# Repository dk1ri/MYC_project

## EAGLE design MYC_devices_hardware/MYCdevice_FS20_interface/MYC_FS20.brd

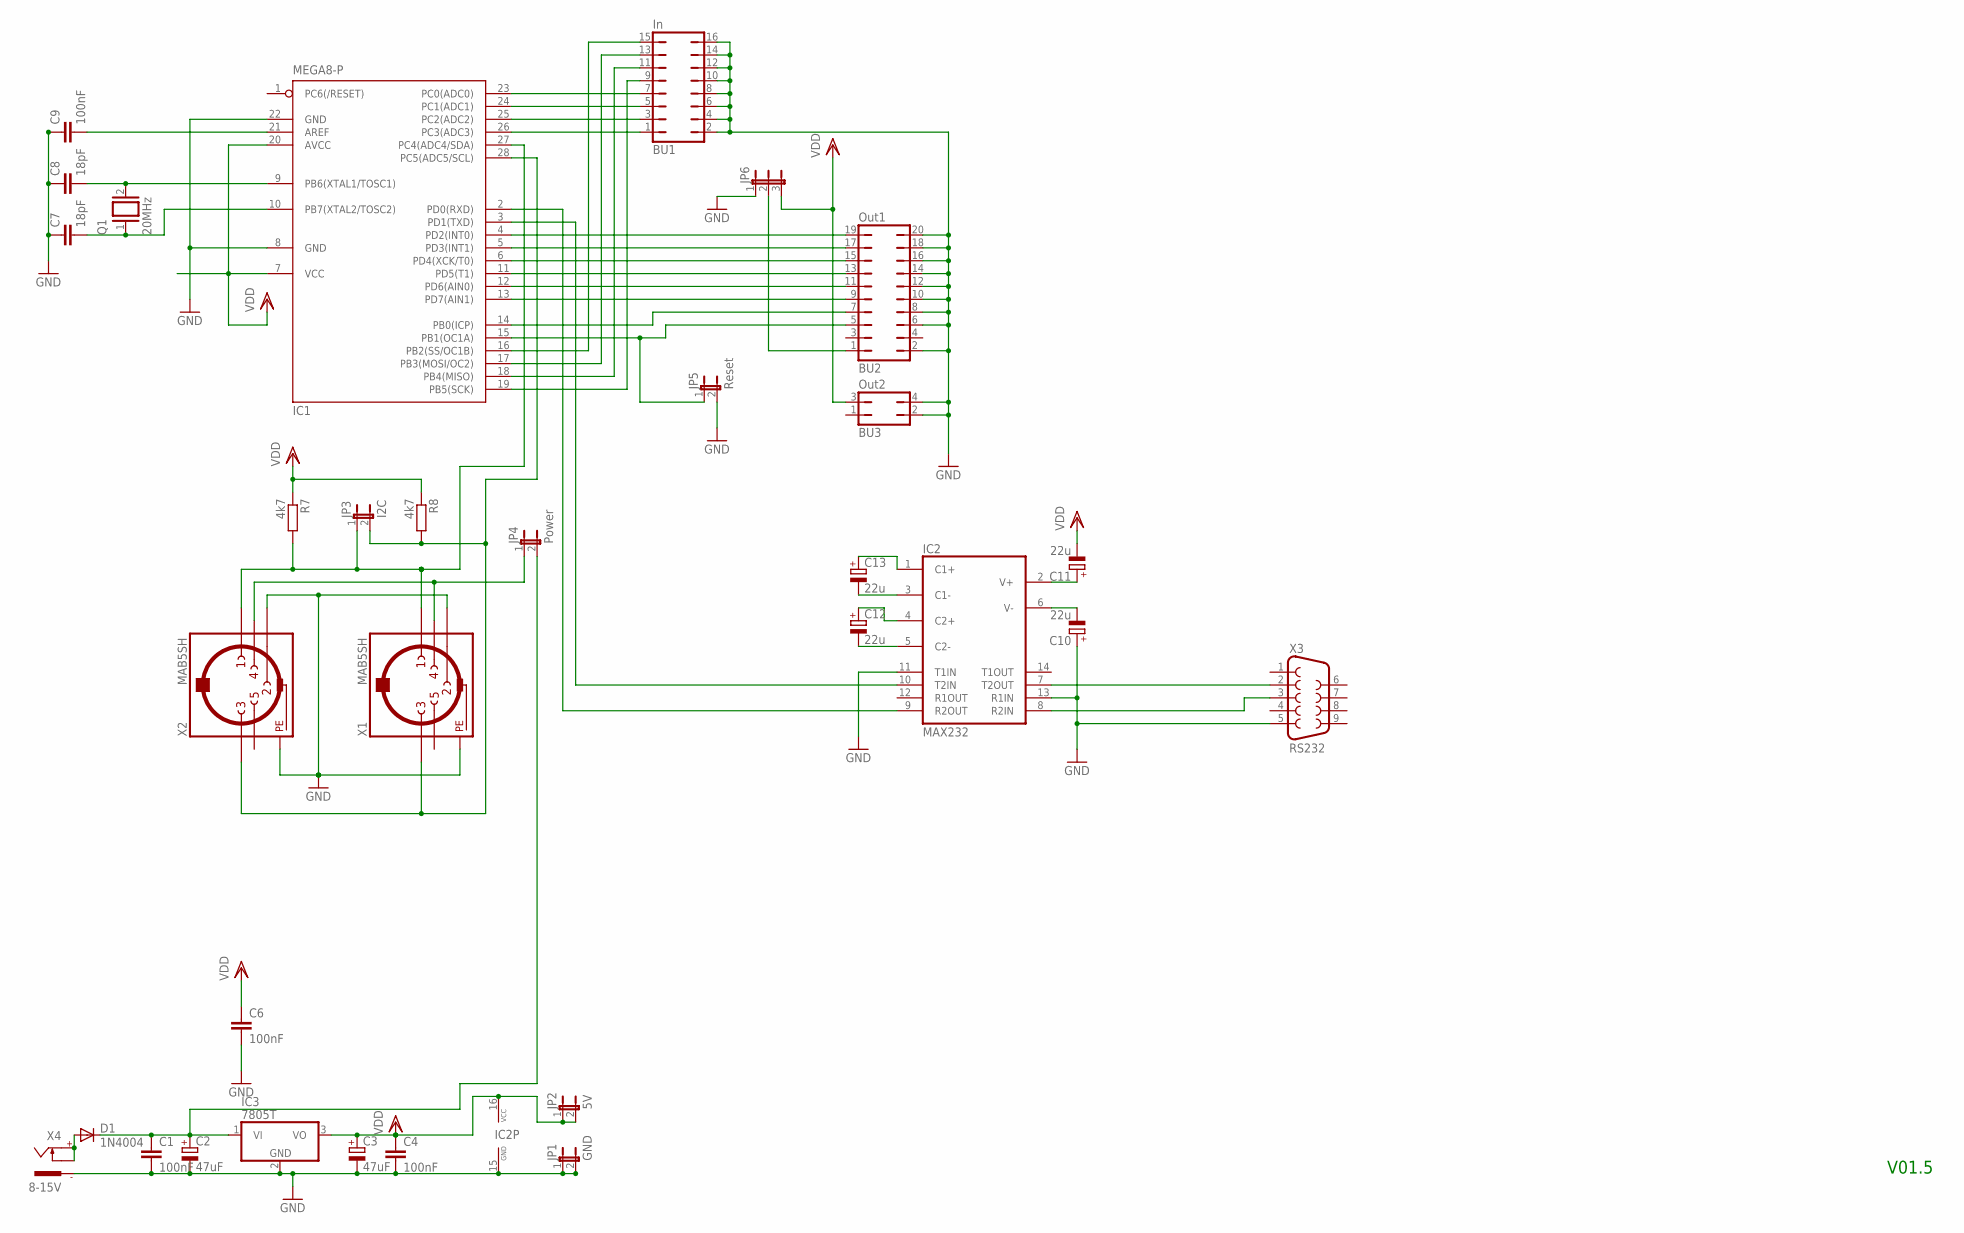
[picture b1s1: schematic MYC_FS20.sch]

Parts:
BU1: In; JP8Q
BU2: Out1; JP10Q
BU3: Out2; JP2Q
C1, C4, C6, C9: 100nF; C050-025X075
C2, C3: 47uF; TT5D10
C7, C8: 18pF; C050-025X075
C10, C11, C12, C13: 22u; TT5D7
D1: 1N4004; DO41-10
IC1: MEGA8-P; DIL28-3
IC2: MAX232; DIL16
IC3: 7805T; TO220H
JP1: GND; JP1
JP2: 5V; JP1
JP3: I2C; JP1
JP4: Power; JP1
JP5: Reset; JP1
JP6: JP2E; JP2
Q1: 20MHz; QS
R7, R8: 4k7; 0207/5V
X1, X2: MAB5SH
X3: RS232; F09H
X4: 8-15V; 737992-5

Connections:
C13: C13.+, IC2.1 (C1+)
GND: BU1.2, BU1.4, BU1.6, BU1.8, BU1.10, BU1.12, BU1.14, BU1.16, BU2.2, BU2.6, BU2.8, BU2.10, BU2.12, BU2.14, BU2.16, BU2.18, BU2.20, BU3.2, BU3.4, C1.2, C2.-, C3.-, C4.2, C6.2, C7.1, C8.1, C9.1, C10.+, IC1.8 (GND), IC1.22 (GND), IC2.11 (T1IN), IC2.13 (R1IN), IC2.15 (GND), IC3.2 (GND), JP1.1, JP1.2, JP5.2, JP6.1, X1.2, X1.PE, X1.PE@ (PE), X2.2, X2.PE, X2.PE@ (PE), X3.5, X4.-1
unnamed: JP4.1, X1.4, X2.4
unnamed: IC1.2 (PD0(RXD)), IC2.9 (R2OUT)
unnamed: C12.-, IC2.5 (C2-)
unnamed: BU2.11, IC1.12 (PD6(AIN0))
unnamed: IC1.27 (PC4(ADC4/SDA)), JP3.1, R7.2, X1.1, X2.1
unnamed: BU1.1, IC1.26 (PC3(ADC3))
unnamed: D1.A, X4.+, X4.K
unnamed: BU2.7, IC1.14 (PB0(ICP))
unnamed: BU2.1, JP6.2
unnamed: IC2.8 (R2IN), X3.3
unnamed: IC1.3 (PD1(TXD)), IC2.10 (T2IN)
unnamed: C12.+, IC2.4 (C2+)
unnamed: C13.-, IC2.3 (C1-)
unnamed: BU1.3, IC1.25 (PC2(ADC2))
unnamed: C11.+, IC2.2 (V+)
unnamed: C10.-, IC2.6 (V-)
unnamed: BU2.5, IC1.15 (PB1(OC1A)), JP5.1
unnamed: C8.2, IC1.9 (PB6(XTAL1/TOSC1)), Q1.2
unnamed: BU1.5, IC1.24 (PC1(ADC1))
unnamed: BU2.9, IC1.13 (PD7(AIN1))
unnamed: IC1.28 (PC5(ADC5/SCL)), JP3.2, R8.2, X1.3, X2.3
unnamed: BU1.7, IC1.23 (PC0(ADC0))
unnamed: BU2.13, IC1.11 (PD5(T1))
unnamed: BU2.15, IC1.6 (PD4(XCK/T0))
unnamed: IC2.7 (T2OUT), X3.2
unnamed: BU2.17, IC1.5 (PD3(INT1))
unnamed: BU2.19, IC1.4 (PD2(INT0))
unnamed: BU1.15, IC1.16 (PB2(SS/OC1B))
unnamed: C1.1, C2.+, D1.C, IC3.1 (VI), JP4.2
unnamed: BU1.13, IC1.17 (PB3(MOSI/OC2))
unnamed: C9.2, IC1.21 (AREF)
unnamed: BU1.11, IC1.18 (PB4(MISO))
unnamed: C7.2, IC1.10 (PB7(XTAL2/TOSC2)), Q1.1
unnamed: BU1.9, IC1.19 (PB5(SCK))
VDD: BU3.3, C3.+, C4.1, C6.1, C11.-, IC1.7 (VCC), IC1.20 (AVCC), IC2.16 (VCC), IC3.3 (VO), JP2.1, JP2.2, JP6.3, R7.1, R8.1

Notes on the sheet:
V01.5

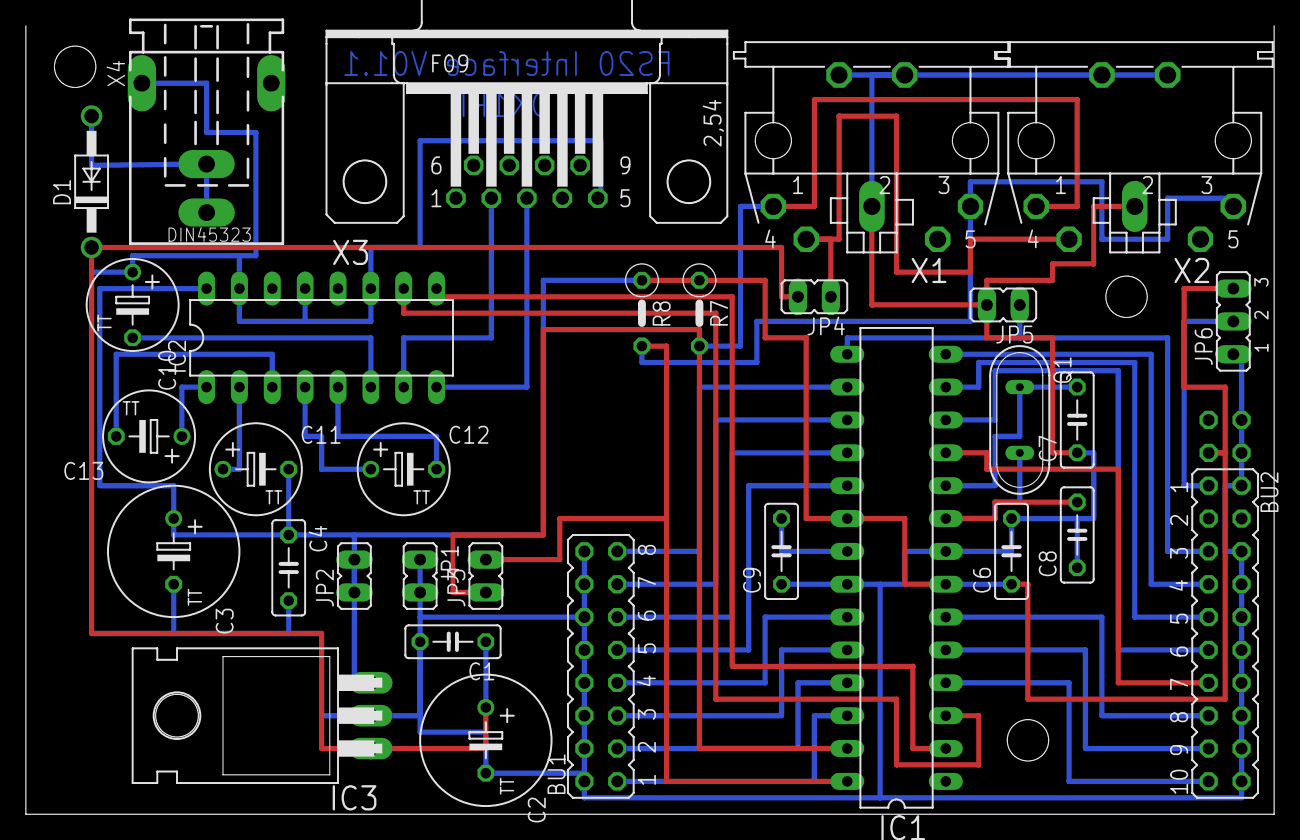
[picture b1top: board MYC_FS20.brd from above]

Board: 2 copper layers, 96.5 x 60.9 mm, 32 parts (1 on the bottom side), 37 nets.

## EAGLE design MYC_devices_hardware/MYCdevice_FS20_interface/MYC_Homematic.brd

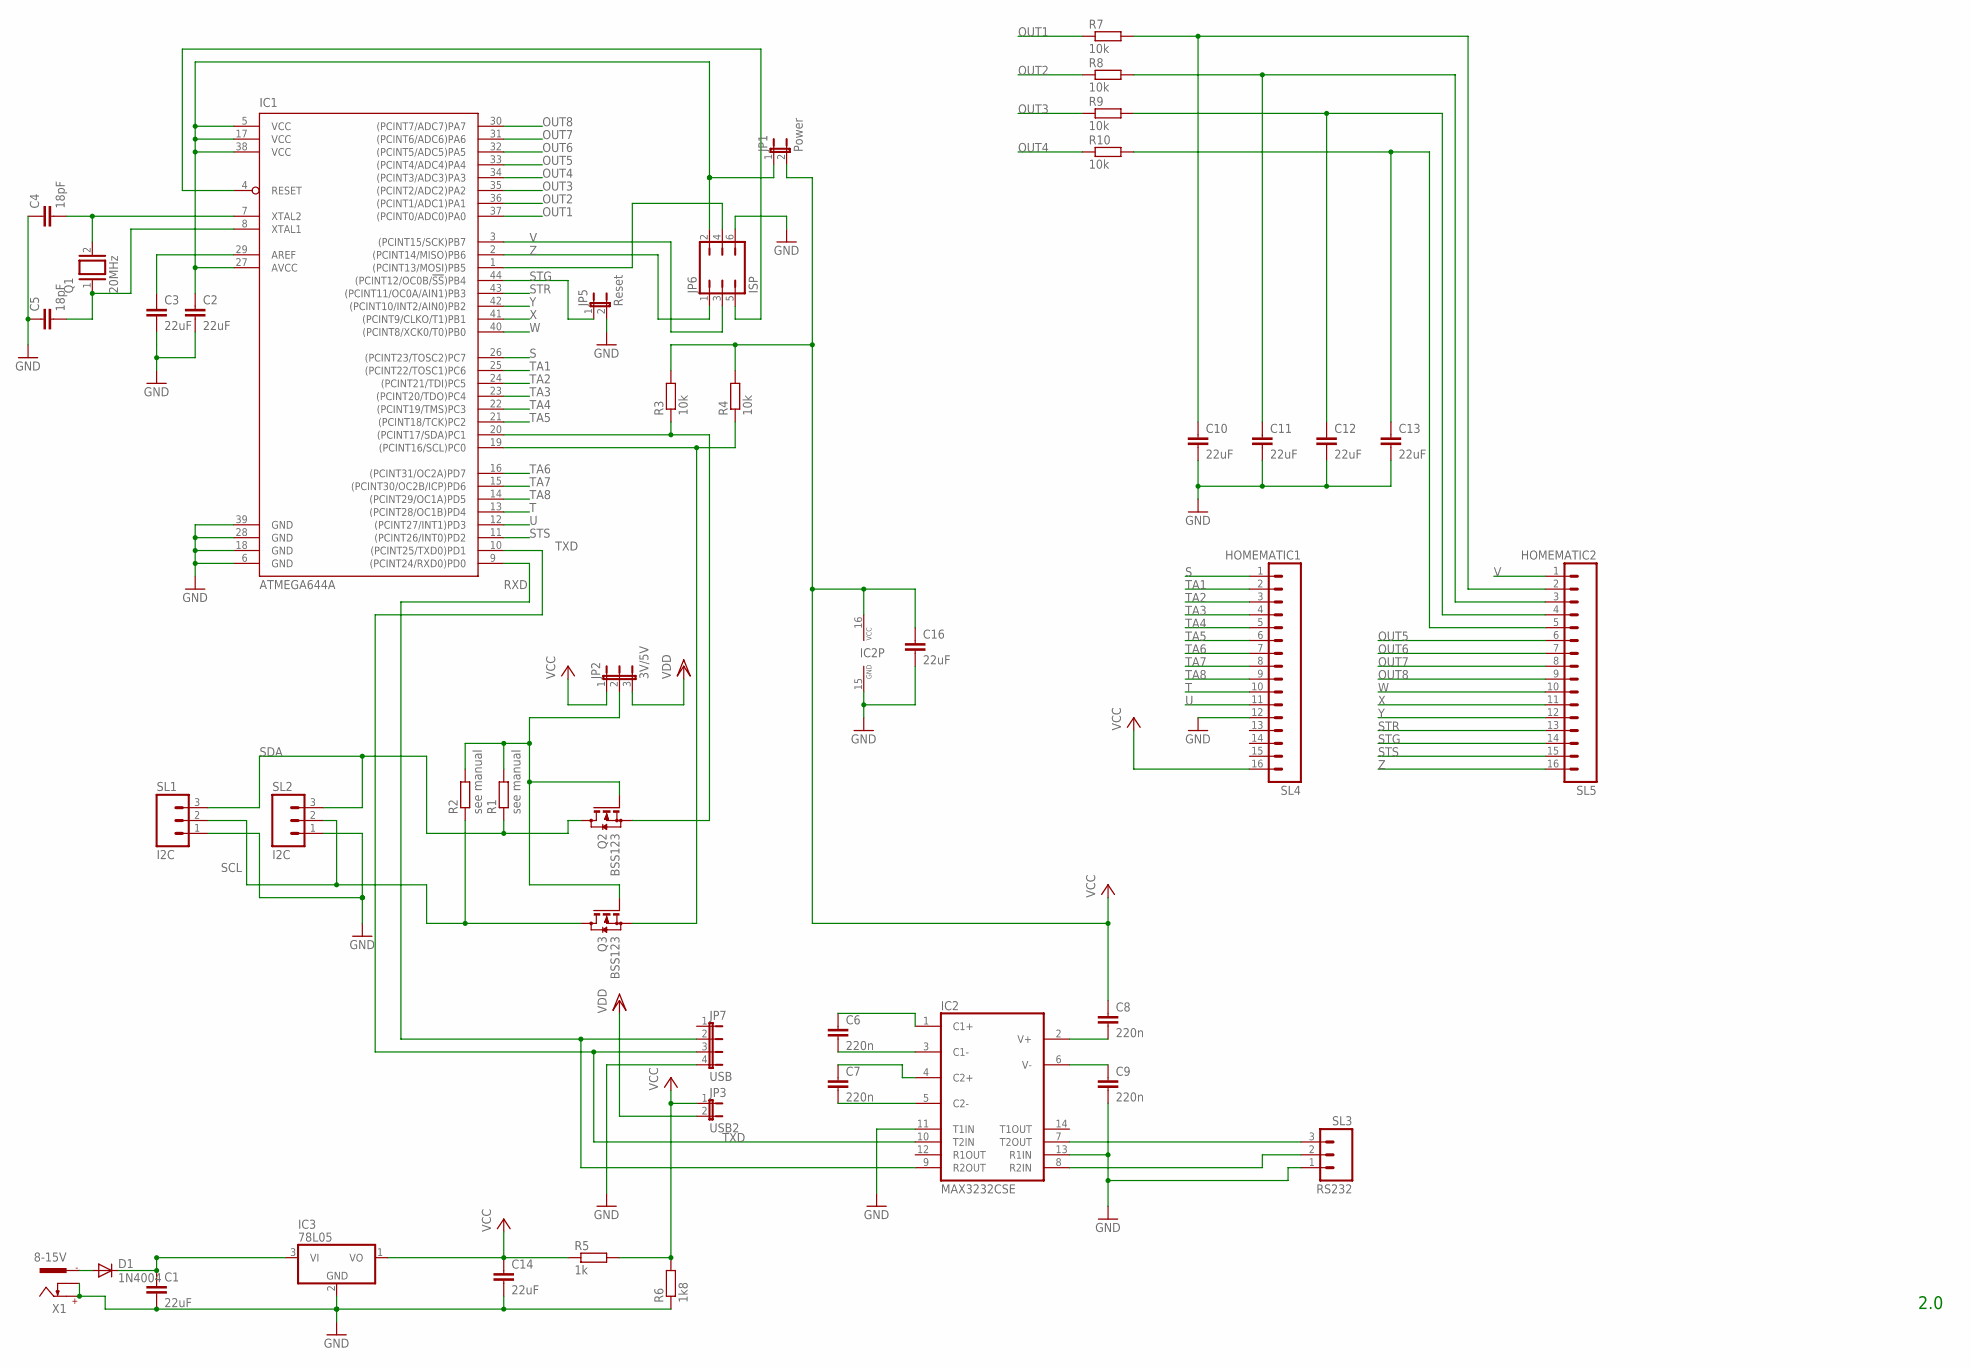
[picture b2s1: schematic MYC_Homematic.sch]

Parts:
C1, C2, C3, C10, C11, C12, C13, C14, C16: 22uF; C1206
C4, C5: 18pF; C025-030X050
C6, C7, C8, C9: 220n; C1206
D1: 1N4004; DO41-10
IC1: ATMEGA644A; TQFP44
IC2: MAX3232CSE; SO16
IC3: 78L05; TO92
JP1: Power; JP1
JP2: 3V/5V; JP2
JP3: USB2; JP1
JP5: Reset; JP1
JP6: ISP; JP3Q
JP7: USB; JP4
Q1: 20MHz; QS
Q2, Q3: BSS123; SOT23
R1, R2: see manual; R1206
R3, R4, R7, R8, R9, R10: 10k; R1206
R5: 1k; R1206
R6: 1k8; R1206
SL1, SL2: I2C; 03P
SL3: RS232; 03P
SL4: HOMEMATIC1; 16P
SL5: HOMEMATIC2; 16P
X1: 8-15V; 737992-5

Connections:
C13: C6.1, IC2.1 (C1+)
GND: C1.2, C2.2, C3.2, C4.1, C5.1, C9.2, C10.2, C11.2, C12.2, C13.2, C14.2, C16.2, IC1.6 (GND), IC1.18 (GND), IC1.28 (GND), IC1.39 (GND), IC2.11 (T1IN), IC2.13 (R1IN), IC2.15 (GND), IC3.2 (GND), JP5.2, JP6.6, JP7.4, R6.1, SL1.1, SL2.1, SL3.1, SL4.12, X1.+, X1.K
unnamed: C1.1, D1.C, IC3.3 (VI)
unnamed: C7.2, IC2.5 (C2-)
unnamed: JP2.2, Q2.1 (G), Q3.1 (G), R1.2, R2.2
unnamed: IC1.19 ((PCINT16/SCL)PC0), Q3.2 (S), R4.1
unnamed: C3.1, IC1.29 (AREF)
unnamed: C2.1, IC1.5 (VCC), IC1.17 (VCC), IC1.27 (AVCC), IC1.38 (VCC), JP1.1, JP6.2
unnamed: IC1.20 ((PCINT17/SDA)PC1), Q2.2 (S), R3.1
unnamed: D1.A, X1.-1
unnamed: IC2.8 (R2IN), SL3.2
unnamed: IC1.1 ((PCINT13/MOSI)PB5), JP6.4
unnamed: C7.1, IC2.4 (C2+)
unnamed: C6.2, IC2.3 (C1-)
unnamed: C10.1, R7.2, SL5.2
unnamed: C8.2, IC2.2 (V+)
unnamed: C9.1, IC2.6 (V-)
unnamed: C4.2, IC1.7 (XTAL2), Q1.2
unnamed: C11.1, R8.2, SL5.3
unnamed: C12.1, R9.2, SL5.4
unnamed: C13.1, R10.2, SL5.5
unnamed: IC1.4 (RESET), JP6.5
unnamed: IC2.7 (T2OUT), SL3.3
unnamed: C5.2, IC1.8 (XTAL1), Q1.1
OUT1: IC1.37 ((PCINT0/ADC0)PA0), R7.1
OUT2: IC1.36 ((PCINT1/ADC1)PA1), R8.1
OUT3: IC1.35 ((PCINT2/ADC2)PA2), R9.1
OUT4: IC1.34 ((PCINT3/ADC3)PA3), R10.1
OUT5: IC1.33 ((PCINT4/ADC4)PA4), SL5.6
OUT6: IC1.32 ((PCINT5/ADC5)PA5), SL5.7
OUT7: IC1.31 ((PCINT6/ADC6)PA6), SL5.8
OUT8: IC1.30 ((PCINT7/ADC7)PA7), SL5.9
RXD: IC1.9 ((PCINT24/RXD0)PD0), IC2.9 (R2OUT), JP7.2
S: IC1.26 ((PCINT23/TOSC2)PC7), SL4.1
SCL: Q3.3 (D), R2.1, SL1.2, SL2.2
SDA: Q2.3 (D), R1.1, SL1.3, SL2.3
STG: IC1.44 ((PCINT12/OC0B/!SS!)PB4), JP5.1, SL5.14
STR: IC1.43 ((PCINT11/OC0A/AIN1)PB3), SL5.13
STS: IC1.11 ((PCINT26/INT0)PD2), SL5.15
T: IC1.13 ((PCINT28/OC1B)PD4), SL4.10
TA1: IC1.25 ((PCINT22/TOSC1)PC6), SL4.2
TA2: IC1.24 ((PCINT21/TDI)PC5), SL4.3
TA3: IC1.23 ((PCINT20/TDO)PC4), SL4.4
TA4: IC1.22 ((PCINT19/TMS)PC3), SL4.5
TA5: IC1.21 ((PCINT18/TCK)PC2), SL4.6
TA6: IC1.16 ((PCINT31/OC2A)PD7), SL4.7
TA7: IC1.15 ((PCINT30/OC2B/ICP)PD6), SL4.8
TA8: IC1.14 ((PCINT29/OC1A)PD5), SL4.9
TXD: IC1.10 ((PCINT25/TXD0)PD1), IC2.10 (T2IN), JP7.3
U: IC1.12 ((PCINT27/INT1)PD3), SL4.11
V: IC1.3 ((PCINT15/SCK)PB7), JP6.3, SL5.1
VCC: C8.1, C14.1, C16.1, IC2.16 (VCC), IC3.1 (VO), JP1.2, JP2.1, JP3.1, R3.2, R4.2, R5.1, R5.2, R6.2, SL4.16
VDD: JP2.3, JP3.2
W: IC1.40 ((PCINT8/XCK0/T0)PB0), SL5.10
X: IC1.41 ((PCINT9/CLKO/T1)PB1), SL5.11
Y: IC1.42 ((PCINT10/INT2/AIN0)PB2), SL5.12
Z: IC1.2 ((PCINT14/MISO)PB6), JP6.1, SL5.16

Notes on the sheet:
2.0

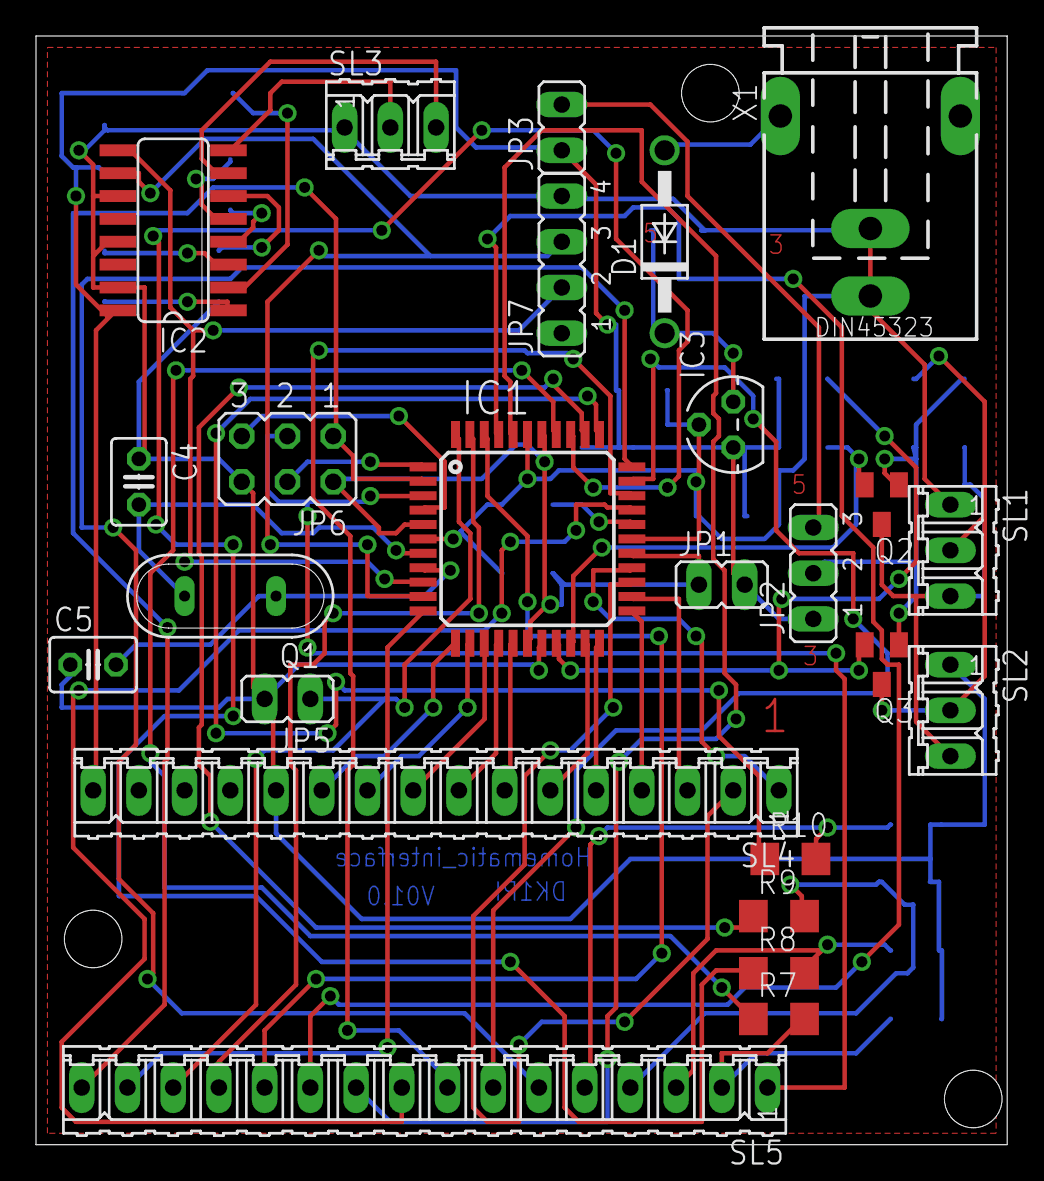
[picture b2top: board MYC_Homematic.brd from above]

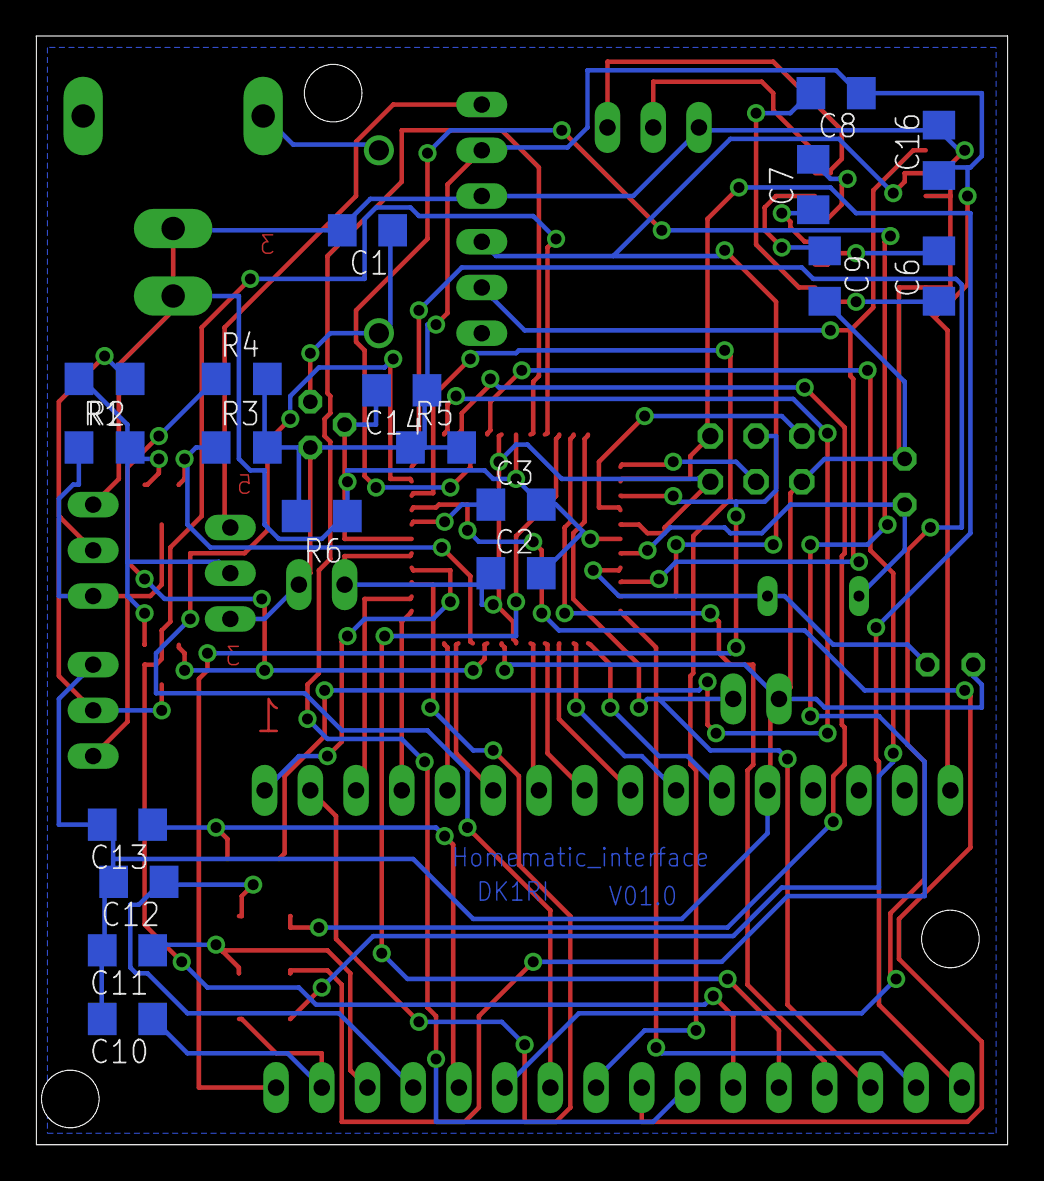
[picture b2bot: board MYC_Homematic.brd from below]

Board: 2 copper layers, 54.0 x 61.6 mm, 44 parts (19 on the bottom side), 57 nets.

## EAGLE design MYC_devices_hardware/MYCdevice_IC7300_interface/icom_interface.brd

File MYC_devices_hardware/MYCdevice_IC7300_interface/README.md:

MYC Interface IC7300 radio

This is a device, which control a radio.

Up to now the software version and the board for a hardware version is available (firmware missing)

For details of the MYC protocol see the documentation or read www.dk1ri.de -> MYC

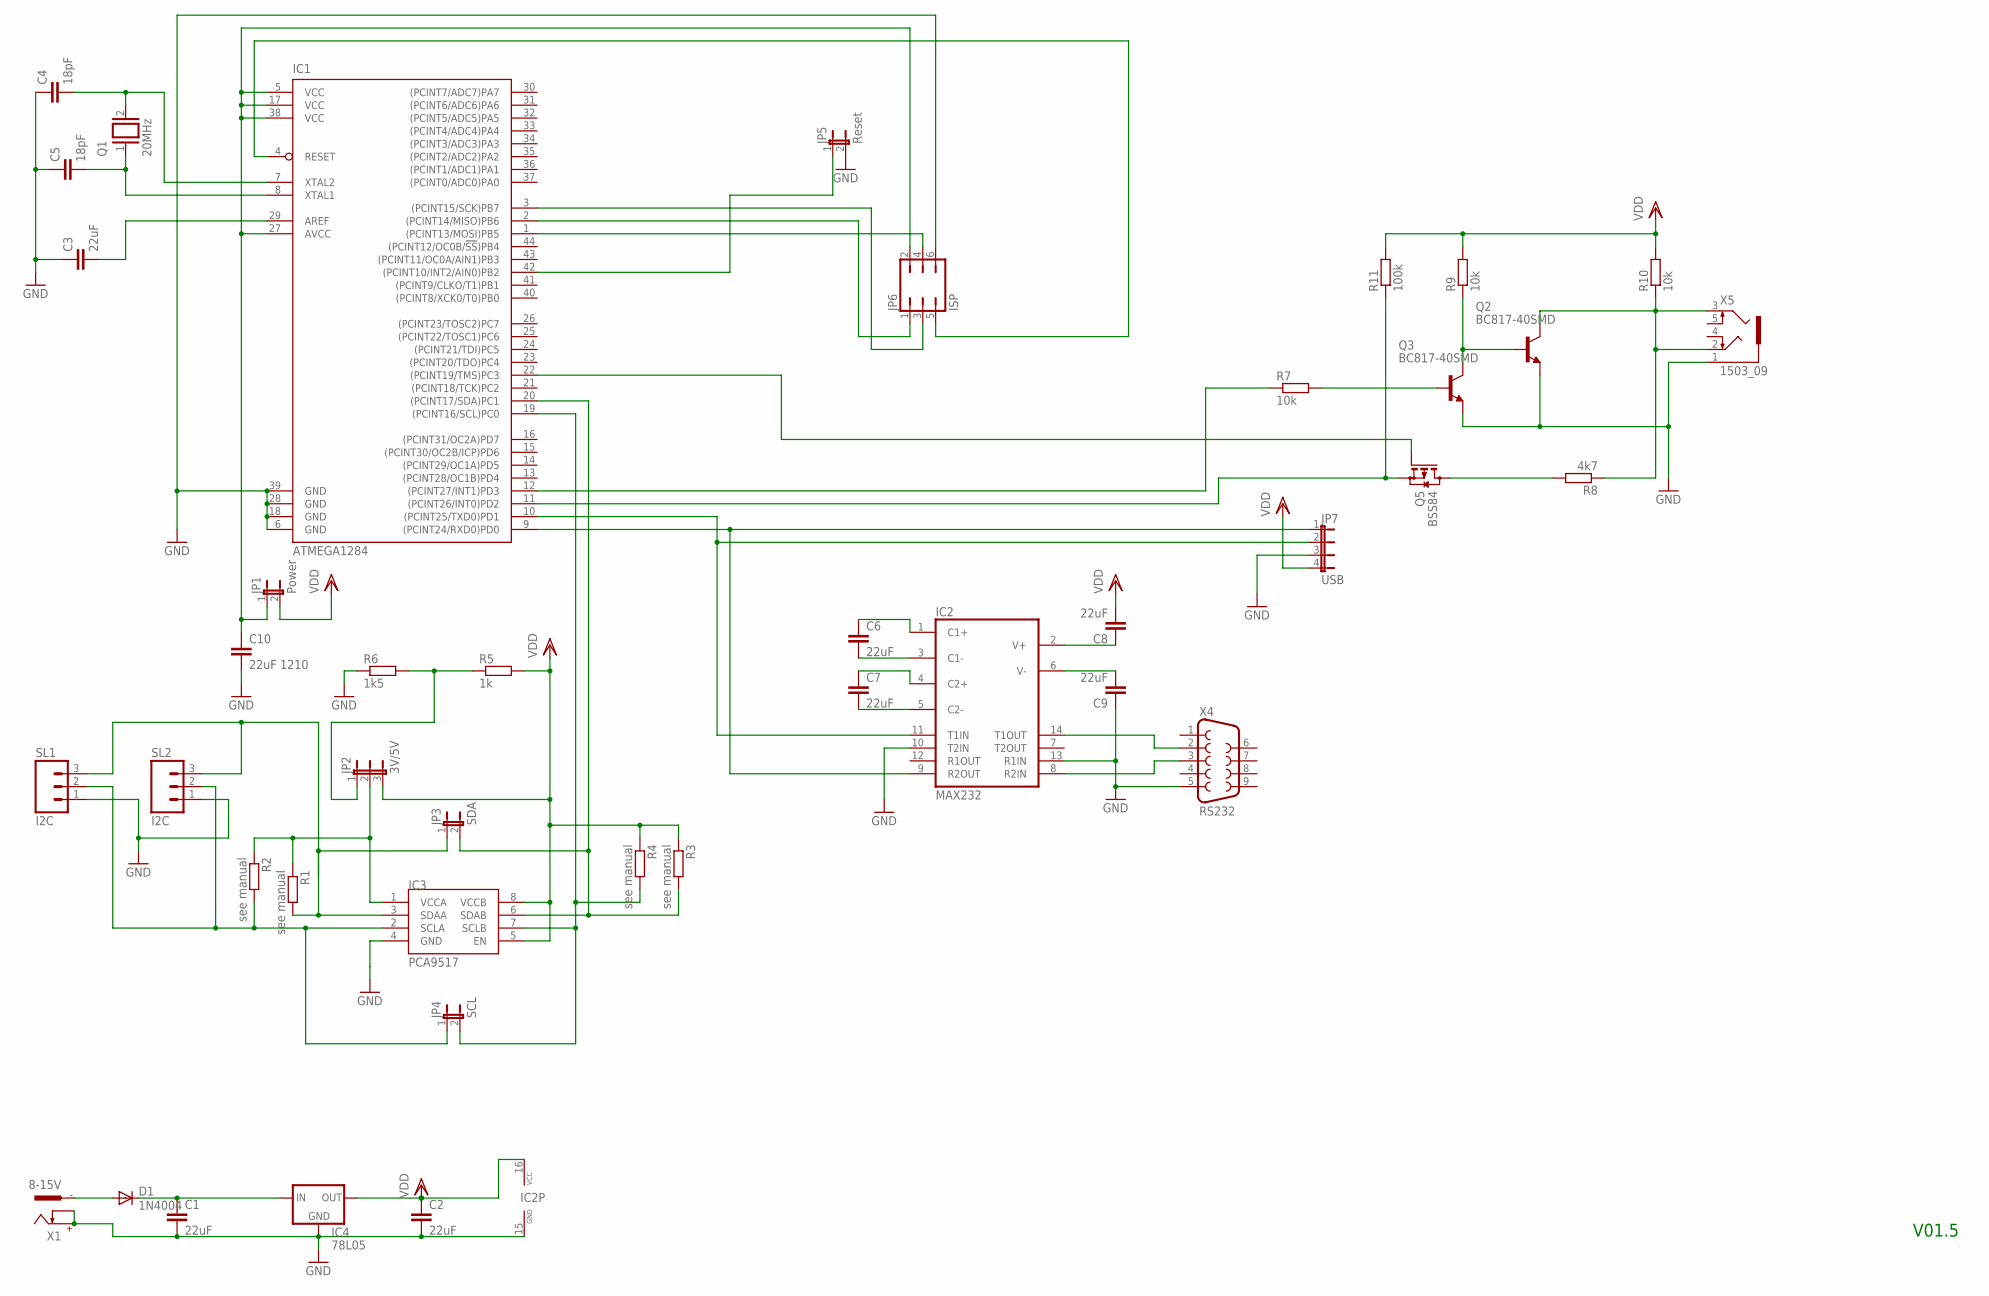
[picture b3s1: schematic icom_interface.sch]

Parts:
C1, C2, C3, C6, C7, C8, C9: 22uF; C1206
C4, C5: 18pF; C025-025X050
C10: 22uF 1210; C1206
D1: 1N4004; DO41-10
IC1: ATMEGA1284; TQFP44
IC2: MAX232; DIL16
IC3: PCA9517; SO-08
IC4: 78L05; 78LXX
JP1: Power; JP1
JP2: 3V/5V; JP2
JP3: SDA; JP1
JP4: SCL; JP1
JP5: Reset; JP1
JP6: ISP; JP3Q
JP7: USB; JP4
Q1: 20MHz; QS
Q2, Q3: BC817-40SMD; SOT23-BEC
Q5: BSS84; SOT23
R1, R2, R3, R4: see manual; R1206
R5: 1k; R1206
R6: 1k5; R1206
R7, R9, R10: 10k; R1206
R8: 4k7; R1206
R11: 100k; R1206
SL1, SL2: I2C; 03P
X1: 8-15V; 737992-5
X4: RS232; F09H
X5: 1503_09

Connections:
C13: C6.1, IC2.1 (C1+)
GND: C1.2, C2.2, C3.1, C4.1, C5.1, C9.1, C10.2, IC1.6 (GND), IC1.18 (GND), IC1.28 (GND), IC1.39 (GND), IC2.10 (T2IN), IC2.13 (R1IN), IC2.15 (GND), IC3.4 (GND), IC4.GND, JP5.2, JP6.6, JP7.3, Q2.E, Q3.E, R6.1, SL1.1, SL2.1, X1.+, X1.K, X4.5, X5.1
unnamed: Q3.B, R7.2
unnamed: IC1.9 ((PCINT24/RXD0)PD0), IC2.9 (R2OUT), JP7.1
unnamed: C7.2, IC2.5 (C2-)
unnamed: IC1.20 ((PCINT17/SDA)PC1), IC3.6 (SDAB), JP3.2, R3.2
unnamed: IC1.2 ((PCINT14/MISO)PB6), JP6.1
unnamed: C10.1, IC1.5 (VCC), IC1.17 (VCC), IC1.27 (AVCC), IC1.38 (VCC), JP1.1, JP6.2
unnamed: C4.2, IC1.7 (XTAL2), Q1.2
unnamed: Q2.C, R8.1, R10.1, X5.2, X5.3
unnamed: IC2.14 (T1OUT), X4.2
unnamed: IC1.12 ((PCINT27/INT1)PD3), R7.1
unnamed: IC1.10 ((PCINT25/TXD0)PD1), IC2.11 (T1IN), JP7.2
unnamed: C7.1, IC2.4 (C2+)
unnamed: C6.2, IC2.3 (C1-)
unnamed: IC1.42 ((PCINT10/INT2/AIN0)PB2), JP5.1
unnamed: C8.1, IC2.2 (V+)
unnamed: C9.2, IC2.6 (V-)
unnamed: IC1.4 (RESET), JP6.5
unnamed: IC1.11 ((PCINT26/INT0)PD2), Q5.2 (S), R11.1
unnamed: IC1.3 ((PCINT15/SCK)PB7), JP6.3
unnamed: C5.2, IC1.8 (XTAL1), Q1.1
unnamed: IC1.19 ((PCINT16/SCL)PC0), IC3.7 (SCLB), JP4.2, R4.2
unnamed: IC3.3 (SDAA), JP3.1, R1.2, SL1.3, SL2.3
unnamed: C3.2, IC1.29 (AREF)
unnamed: IC3.2 (SCLA), JP4.1, R2.2, SL1.2, SL2.2
unnamed: JP2.1, R5.1, R6.2
unnamed: D1.A, X1.-1
unnamed: IC1.1 ((PCINT13/MOSI)PB5), JP6.4
unnamed: Q5.3 (D), R8.2
unnamed: Q2.B, Q3.C, R9.1
unnamed: IC3.1 (VCCA), JP2.2, R1.1, R2.1
unnamed: C1.1, D1.C, IC4.IN
unnamed: IC1.22 ((PCINT19/TMS)PC3), Q5.1 (G)
unnamed: IC2.8 (R2IN), X4.3
VDD: C2.1, C8.2, IC2.16 (VCC), IC3.5 (EN), IC3.8 (VCCB), IC4.OUT, JP1.2, JP2.3, JP7.4, R3.1, R4.1, R5.2, R9.2, R10.2, R11.2

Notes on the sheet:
V01.5

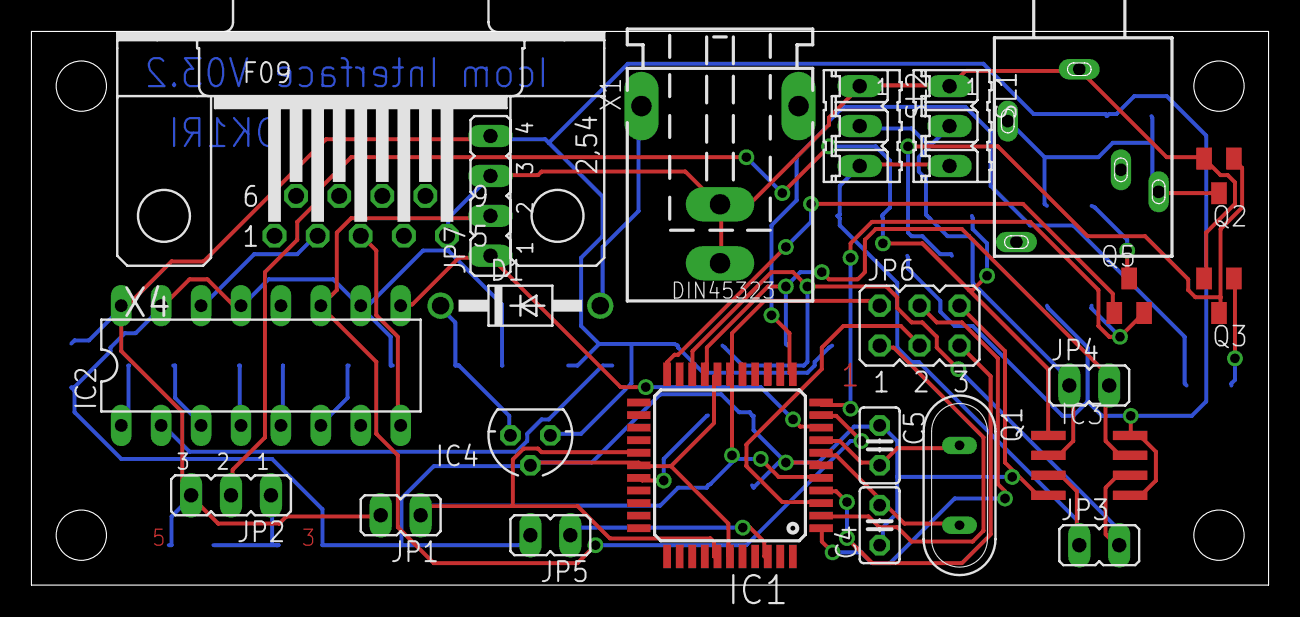
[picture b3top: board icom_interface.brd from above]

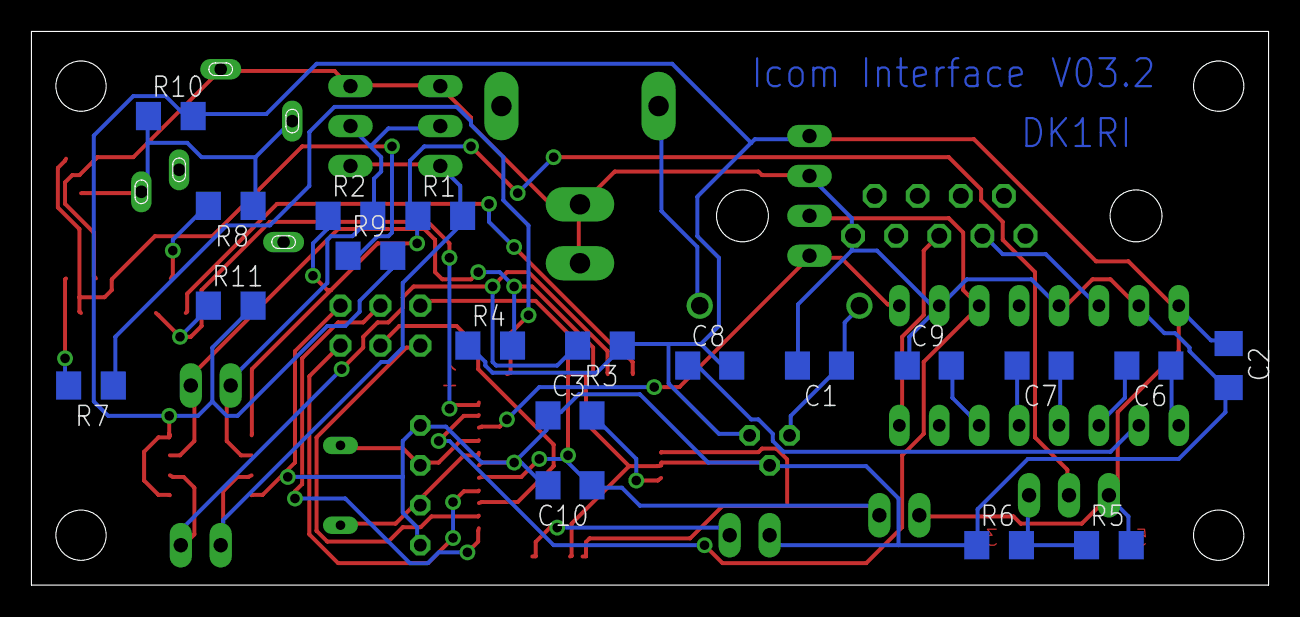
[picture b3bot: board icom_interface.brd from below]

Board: 2 copper layers, 78.7 x 35.2 mm, 42 parts (19 on the bottom side), 36 nets.

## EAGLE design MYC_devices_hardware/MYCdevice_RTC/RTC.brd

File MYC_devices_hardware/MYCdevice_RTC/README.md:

#Real Time Clock
This is a device, which can deliver 
accurate time data to a MYC system

The DCF RTC board by ELV is used, which receives the DCF77 signal from Frankfurt.

For details of the MYC protocol see the documentation or read www.dk1ri.de -> MYC

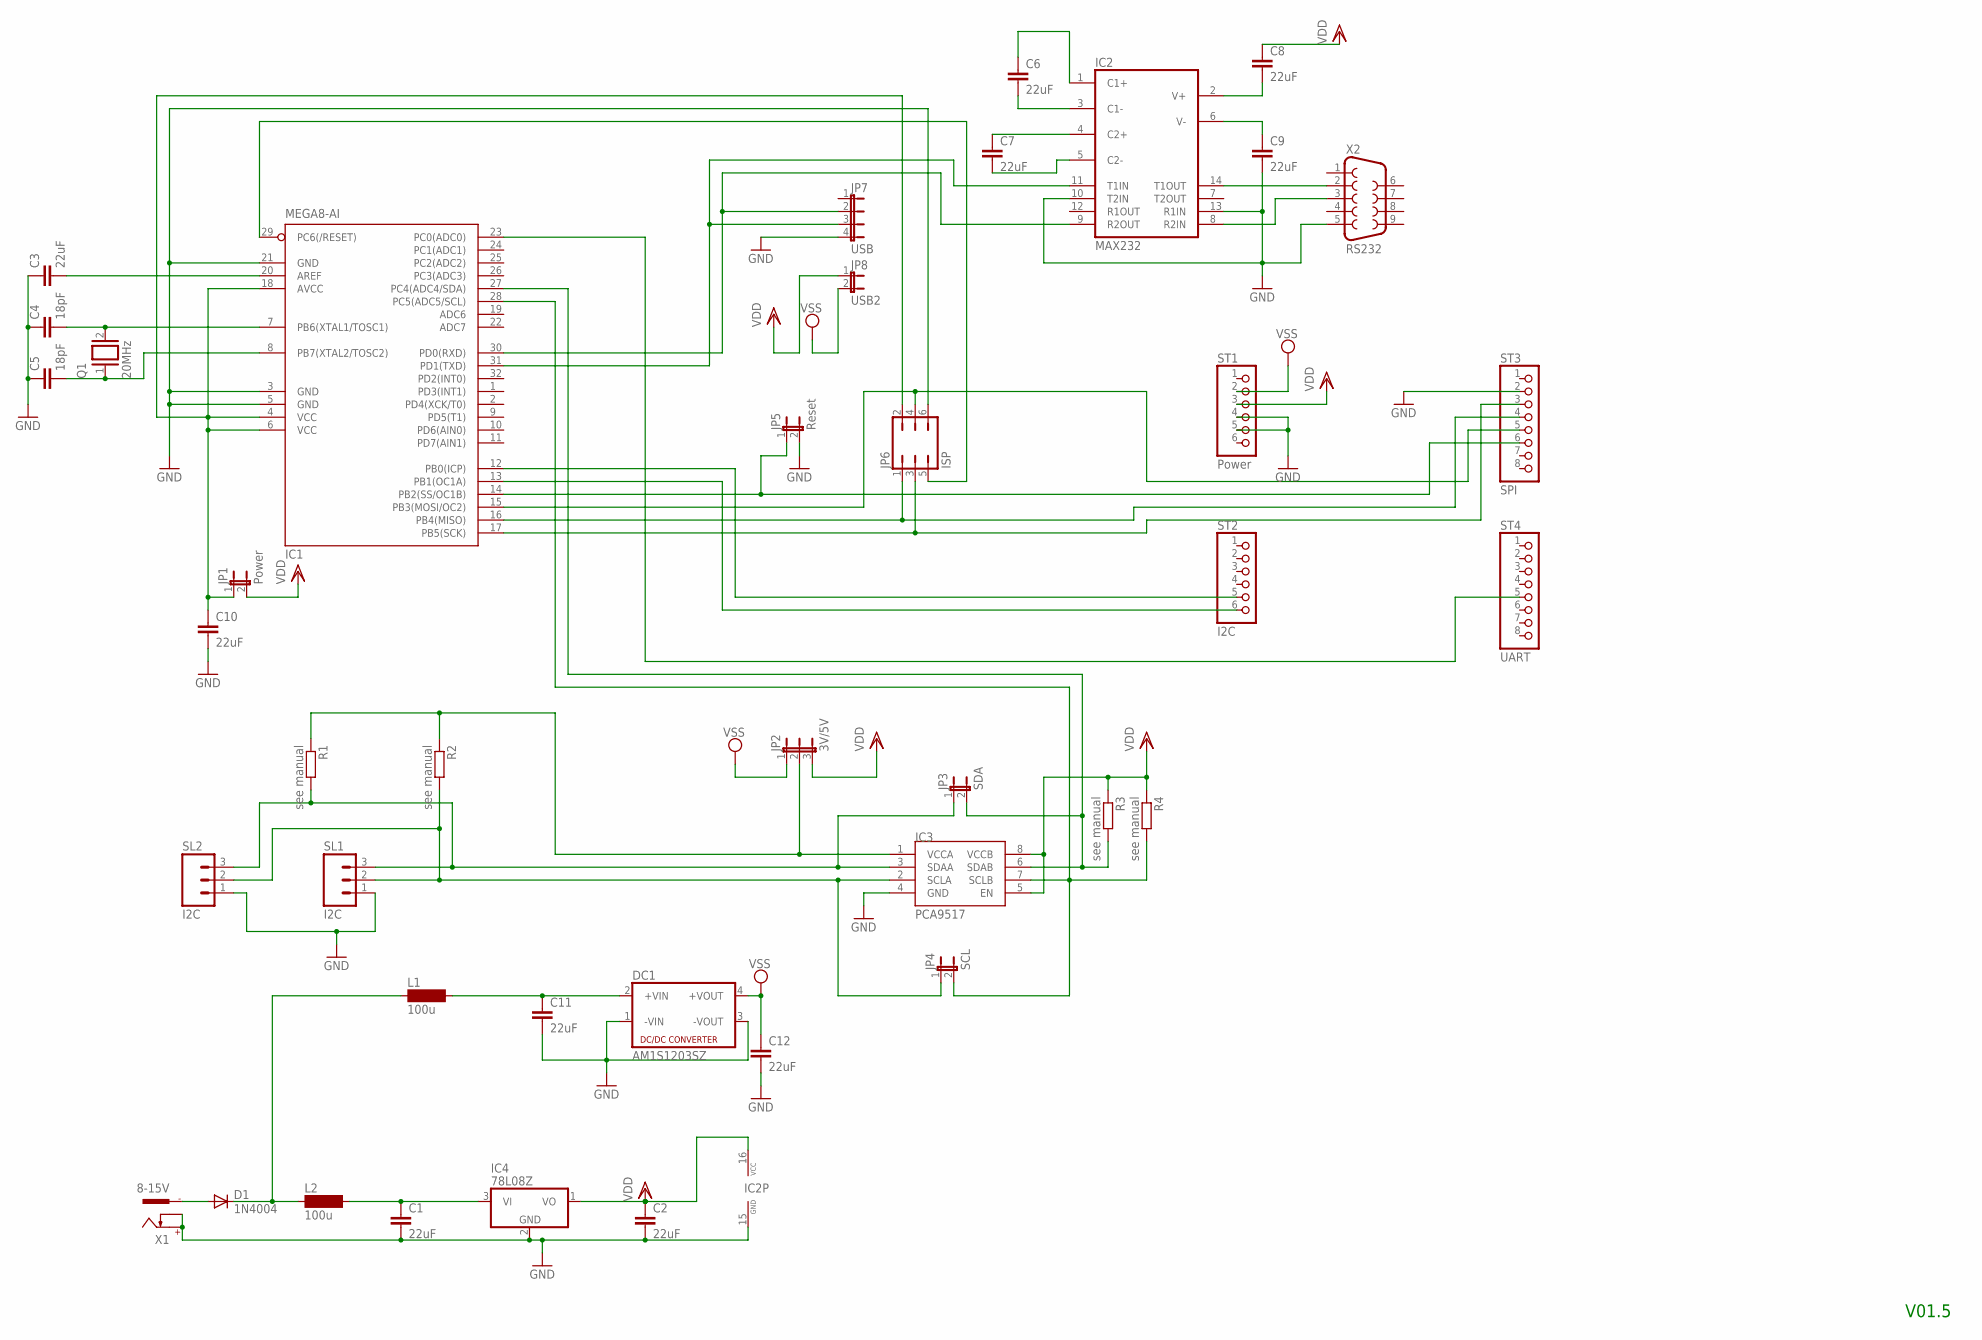
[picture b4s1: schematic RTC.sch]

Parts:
C1, C2, C3, C6, C7, C8, C9, C10, C11, C12: 22uF; C1206
C4, C5: 18pF; C025-025X050
D1: 1N4004; DO41-10
DC1: AM1S1203SZ; NME
IC1: MEGA8-AI; TQFP32-08
IC2: MAX232; DIL16
IC3: PCA9517; SO-08
IC4: 78L08Z; TO92
JP1: Power; JP1
JP2: 3V/5V; JP2
JP3: SDA; JP1
JP4: SCL; JP1
JP5: Reset; JP1
JP6: ISP; JP3Q
JP7: USB; JP4
JP8: USB2; JP1
L1, L2: 100u; MS85
Q1: 20MHz; QS
R1, R2, R3, R4: see manual; R1206
SL1, SL2: I2C; 03P
ST1: Power; 1X06
ST2: I2C; 1X06
ST3: SPI; 1X08
ST4: UART; 1X08
X1: 8-15V; 737992-5
X2: RS232; F09H

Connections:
GND: C1.2, C2.2, C3.1, C4.1, C5.1, C9.2, C10.2, C11.2, C12.2, DC1.1 (-VIN), DC1.3 (-VOUT), IC1.3 (GND), IC1.5 (GND), IC1.21 (GND), IC2.10 (T2IN), IC2.13 (R1IN), IC2.15 (GND), IC3.4 (GND), IC4.2 (GND), JP5.2, JP6.6, JP7.4, SL1.1, SL2.1, ST1.4, ST1.5, ST3.2, X1.+, X1.K, X2.5
unnamed: IC1.23 (PC0(ADC0)), ST4.5
unnamed: IC1.12 (PB0(ICP)), ST2.5
unnamed: C11.1, DC1.2 (+VIN), L1.2
unnamed: IC1.14 (PB2(SS/OC1B)), JP5.1, ST3.6
unnamed: IC1.27 (PC4(ADC4/SDA)), IC3.6 (SDAB), JP3.2, R3.2
unnamed: IC2.8 (R2IN), X2.3
unnamed: D1.C, L1.1, L2.1
unnamed: IC1.31 (PD1(TXD)), IC2.11 (T1IN), JP7.3
unnamed: IC1.30 (PD0(RXD)), IC2.9 (R2OUT), JP7.2
unnamed: IC1.13 (PB1(OC1A)), ST2.6
unnamed: IC3.2 (SCLA), JP4.1, R2.2, SL1.2, SL2.2
unnamed: IC3.3 (SDAA), JP3.1, R1.2, SL1.3, SL2.3
unnamed: IC2.14 (T1OUT), X2.2
unnamed: C8.2, IC2.2 (V+)
unnamed: IC1.16 (PB4(MISO)), JP6.1, ST3.4
unnamed: C9.1, IC2.6 (V-)
unnamed: IC1.29 (PC6(/RESET)), JP6.5
unnamed: C4.2, IC1.7 (PB6(XTAL1/TOSC1)), Q1.2
unnamed: IC1.17 (PB5(SCK)), JP6.3, ST3.3
unnamed: IC3.1 (VCCA), JP2.2, R1.1, R2.1
unnamed: IC1.28 (PC5(ADC5/SCL)), IC3.7 (SCLB), JP4.2, R4.2
unnamed: C6.1, IC2.1 (C1+)
unnamed: C6.2, IC2.3 (C1-)
unnamed: C7.1, IC2.4 (C2+)
unnamed: C7.2, IC2.5 (C2-)
unnamed: D1.A, X1.-1
unnamed: IC1.15 (PB3(MOSI/OC2)), JP6.4, ST3.5
unnamed: C1.1, IC4.3 (VI), L2.2
unnamed: C3.2, IC1.20 (AREF)
unnamed: C5.2, IC1.8 (PB7(XTAL2/TOSC2)), Q1.1
unnamed: C10.1, IC1.4 (VCC), IC1.6 (VCC), IC1.18 (AVCC), JP1.1, JP6.2
VDD: C2.1, C8.1, IC2.16 (VCC), IC3.5 (EN), IC3.8 (VCCB), IC4.1 (VO), JP1.2, JP2.3, JP8.1, R3.1, R4.1, ST1.3
VSS: C12.1, DC1.4 (+VOUT), JP2.1, JP8.2, ST1.2

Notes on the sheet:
V01.5

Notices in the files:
MYC_devices_hardware/MYCdevice_FS20_interface/FS20_8Kanal_sender.bas:
'copyright : DK1RI
'under GPL (Gnu public licence)
